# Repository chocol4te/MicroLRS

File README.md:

# MicroLRS
An OpenLRS compatible PPM receiver. Very minimal design. Uses internal clock on ATMEGA328P and requires socket tool to program. Only output is PPM, but RSSI and other data can be injected. Suitable for long range mini-quads and small UAVs.

Can be found on OSH Park at https://oshpark.com/shared_projects/8gSZM9lk.

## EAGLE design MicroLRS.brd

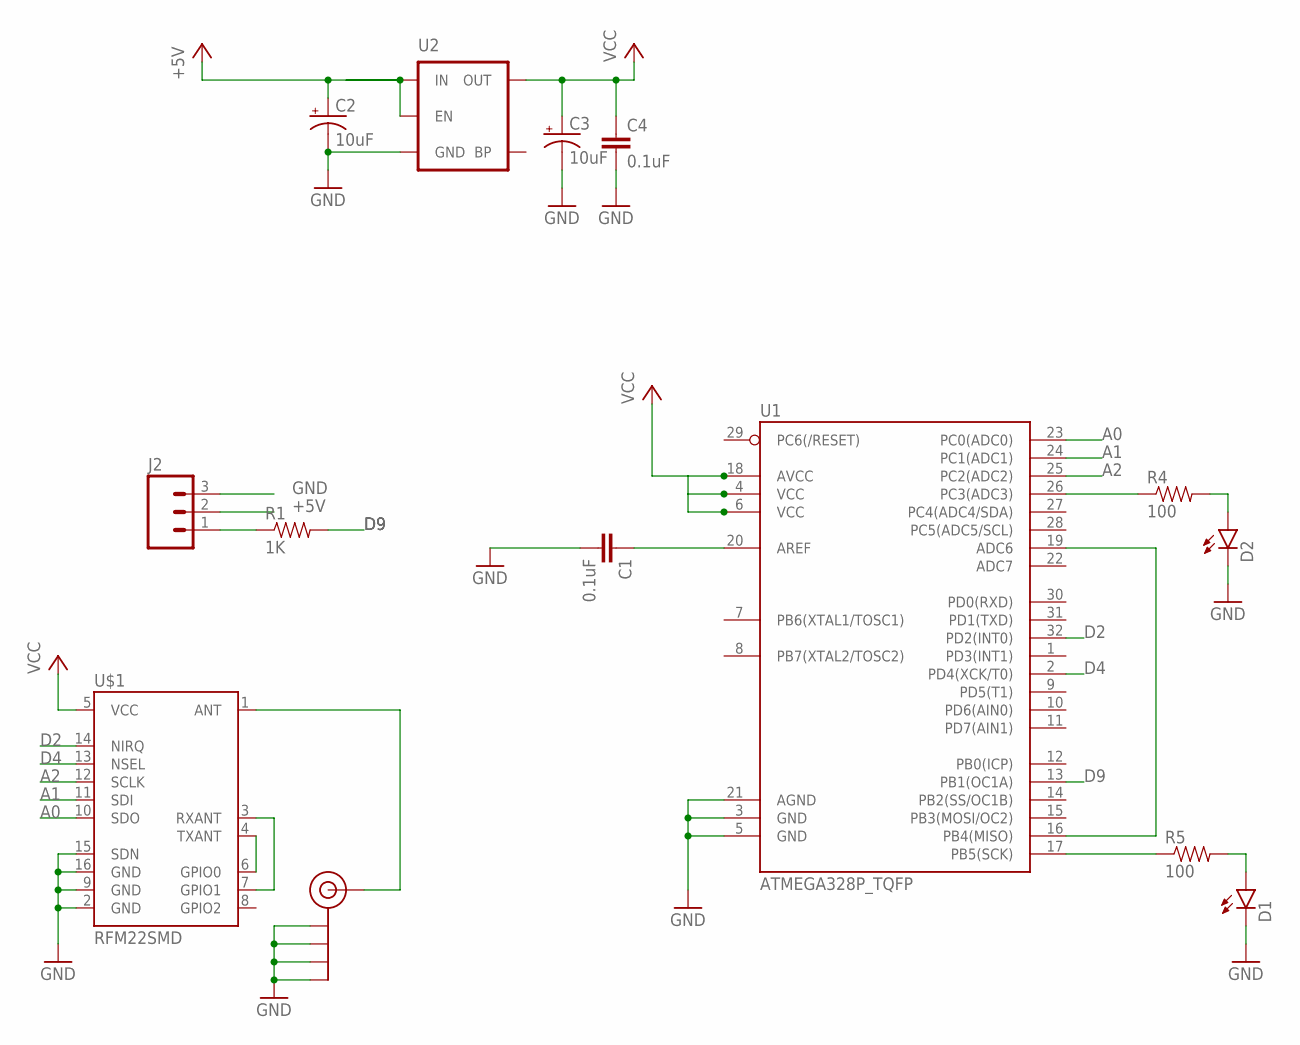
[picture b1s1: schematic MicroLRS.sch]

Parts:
C1: 0.1uF; 0402-CAP
C2, C3: 10uF; 0603-POL
C4: 0.1uF; 0603-CAP
D1, D2: LED0603; LED-0603
J2: M03PTH; 1X03
J$1: SMA_EDGE; SMA-EDGE
R1: 1K; 0603-RES
R4, R5: 100; 0603-RES
U1: ATMEGA328P_TQFP; TQFP32-08
U2: MIC52053.3V; SOT23-5
U$1: RFM22SMD; RFM22-XXX-S2

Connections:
+5V: C2.A (+), J2.2, U2.1 (IN), U2.3 (EN)
A0: U1.23 (PC0(ADC0)), U$1.10 (SDO)
A1: U1.24 (PC1(ADC1)), U$1.11 (SDI)
A2: U1.25 (PC2(ADC2)), U$1.12 (SCLK)
D2: U1.32 (PD2(INT0)), U$1.14 (NIRQ)
D4: U1.2 (PD4(XCK/T0)), U$1.13 (NSEL)
D9: R1.2, U1.13 (PB1(OC1A))
GND: C1.2, C2.K (-), C3.K (-), C4.2, D1.C, D2.C, J2.3, J$1.GND@0 (GND), J$1.GND@1 (GND), J$1.GND@2 (GND), J$1.GND@3 (GND), U1.3 (GND), U1.5 (GND), U1.21 (AGND), U2.2 (GND), U$1.2 (GND), U$1.9 (GND), U$1.15 (SDN), U$1.16 (GND)
unnamed: C1.1, U1.20 (AREF)
unnamed: J$1.SIG (SIGNAL), U$1.1 (ANT)
unnamed: U$1.4 (TXANT), U$1.6 (GPIO0)
unnamed: U$1.3 (RXANT), U$1.7 (GPIO1)
unnamed: U1.16 (PB4(MISO)), U1.19 (ADC6)
unnamed: J2.1, R1.1
unnamed: R4.1, U1.26 (PC3(ADC3))
unnamed: R5.1, U1.17 (PB5(SCK))
unnamed: D2.A, R4.2
unnamed: D1.A, R5.2
VCC: C3.A (+), C4.1, U1.4 (VCC), U1.6 (VCC), U1.18 (AVCC), U2.5 (OUT), U$1.5 (VCC)

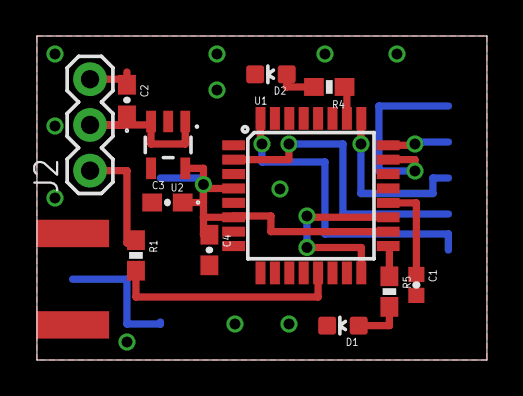
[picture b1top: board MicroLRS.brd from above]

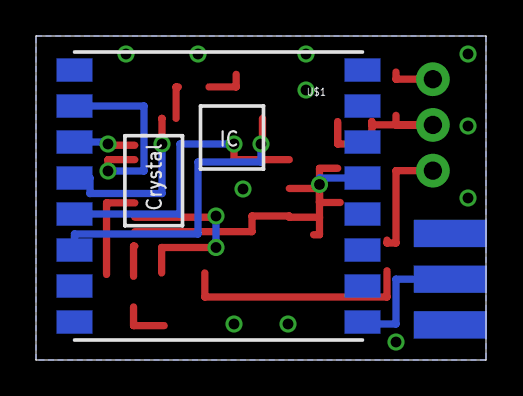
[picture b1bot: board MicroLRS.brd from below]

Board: 2 copper layers, 25.0 x 18.0 mm, 14 parts (2 on the bottom side), 19 nets.

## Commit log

2016-02-07 Initial upload of schematic and board layout

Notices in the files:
parts and their libraries:
SparkFun-Capacitors: Licensing: Creative Commons ShareAlike 4.0 International - https://creativecommons.org/licenses/by-sa/4.0
